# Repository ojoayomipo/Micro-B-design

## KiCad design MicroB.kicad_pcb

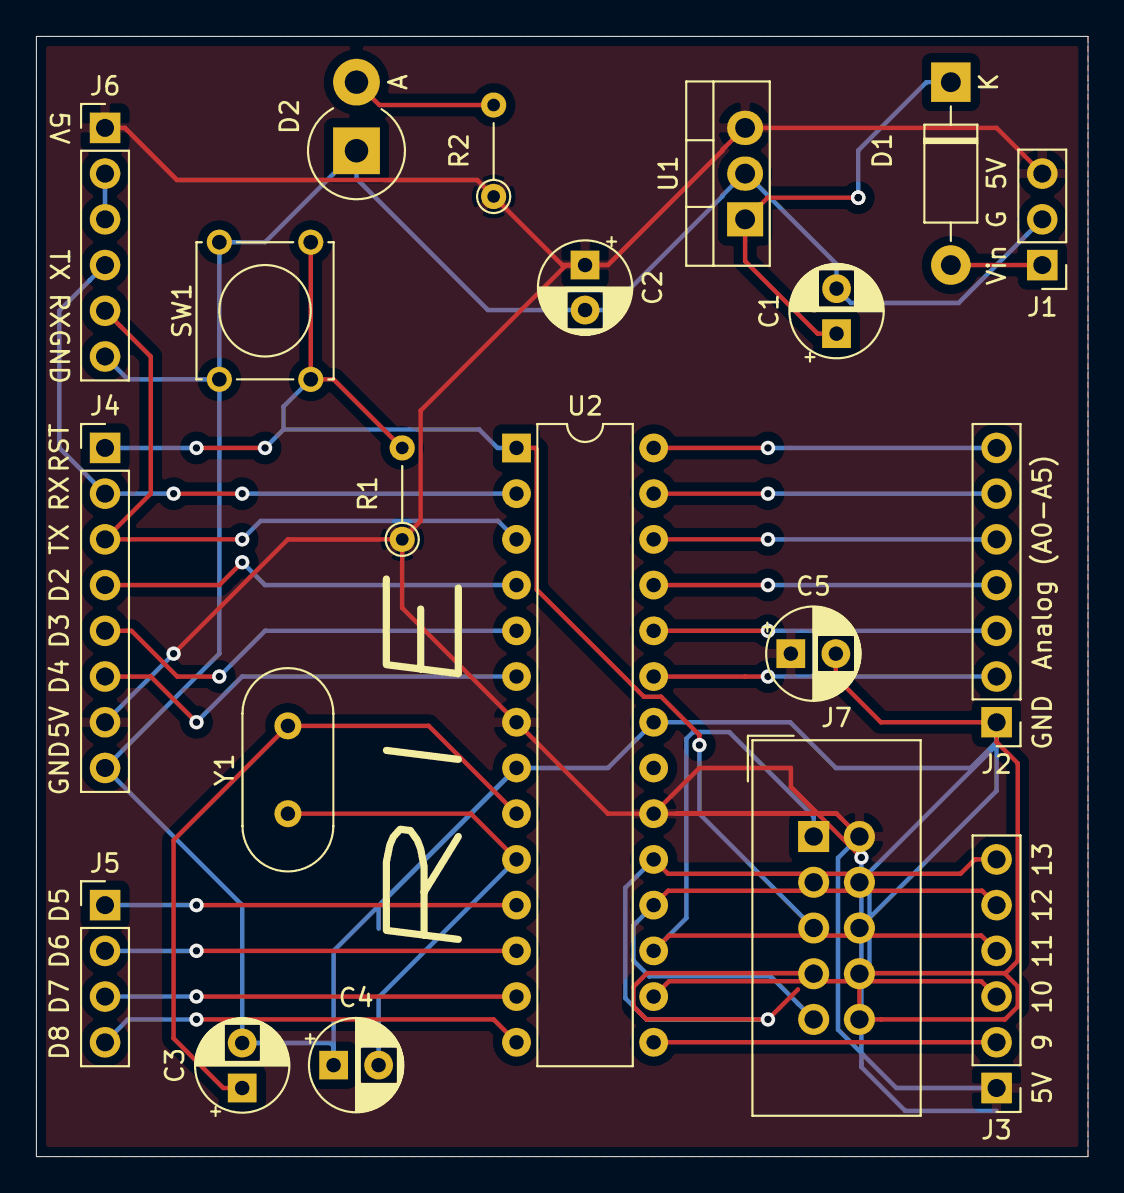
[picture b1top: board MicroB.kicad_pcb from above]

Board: 2 copper layers, 58.4 x 62.2 mm, 20 parts (0 on the bottom side), 29 nets.

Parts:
C1: 100u; CP_Radial_D5.0mm_P2.50mm
C2: 22u; CP_Radial_D5.0mm_P2.50mm
C3, C4: 22p; CP_Radial_D5.0mm_P2.50mm
C5: C; CP_Radial_D5.0mm_P2.50mm
D1: 1N4007; D_DO-41_SOD81_P10.16mm_Horizontal
D2: LED_ALT; D_DO-201_P3.81mm_Vertical_AnodeUp
J1: Conn_01x03_Male; PinHeader_1x03_P2.54mm_Vertical
J2: Conn_01x07_Female; PinHeader_1x07_P2.54mm_Vertical
J3, J6: Conn_01x06_Female; PinHeader_1x06_P2.54mm_Vertical
J4: Conn_01x08_Female; PinHeader_1x08_P2.54mm_Vertical
J5: Conn_01x04_Female; PinHeader_1x04_P2.54mm_Vertical
J7: Conn_02x05_Counter_Clockwise; IDC-Header_2x05_P2.54mm_Vertical
R1: R; R_Axial_DIN0204_L3.6mm_D1.6mm_P5.08mm_Vertical
R2: 220; R_Axial_DIN0204_L3.6mm_D1.6mm_P5.08mm_Vertical
SW1: SW_Push; SW_Tactile_Straight_KSA0Axx1LFTR
U1: LM7805_TO220; TO-220-3_Vertical
U2: ATmega328P-PU; DIP-28_W7.62mm
Y1: Crystal; Crystal_HC49-U_Vertical

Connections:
+5V: C2.1, C5.1, J1.3, J3.1, J4.7, J6.1, J7.2, R1.1, R2.1, U1.3, U2.7, U2.20
D5: J5.1, U2.11
D6: J5.2, U2.12
D8: J5.4, U2.14
GND: C1.2, C2.2, C3.2, C4.1, C5.2, D2.1, J1.2, J2.1, J4.8, J6.6, J7.4, J7.6, J7.8, J7.10, SW1.1, U1.2, U2.8, U2.22
MISO: J3.5, J7.9, U2.18
MOSI: J3.4, J7.1, U2.17
unnamed: C1.1, D1.1, U1.1
unnamed: D1.2, J1.1
unnamed: D2.2, R2.2
unnamed: J2.2, U2.23
unnamed: J2.3, U2.24
unnamed: J2.4, U2.25
unnamed: J2.5, U2.26
unnamed: J2.6, U2.27
unnamed: J2.7, U2.28
unnamed: J3.2, U2.15
unnamed: J3.3, U2.16
unnamed: J4.4, U2.4
unnamed: J4.5, U2.5
unnamed: J4.6, U2.6
unnamed: J5.3, U2.13
unnamed: J6.2, J6.3
RESET: J4.1, J7.5, R1.2, SW1.2, U2.1
RX: J4.2, J6.4, U2.2
SCK: J3.6, J7.7, U2.19
TX: J4.3, J6.5, U2.3
XTAL1: C3.1, U2.9, Y1.2
XTAL2: C4.2, U2.10, Y1.1
